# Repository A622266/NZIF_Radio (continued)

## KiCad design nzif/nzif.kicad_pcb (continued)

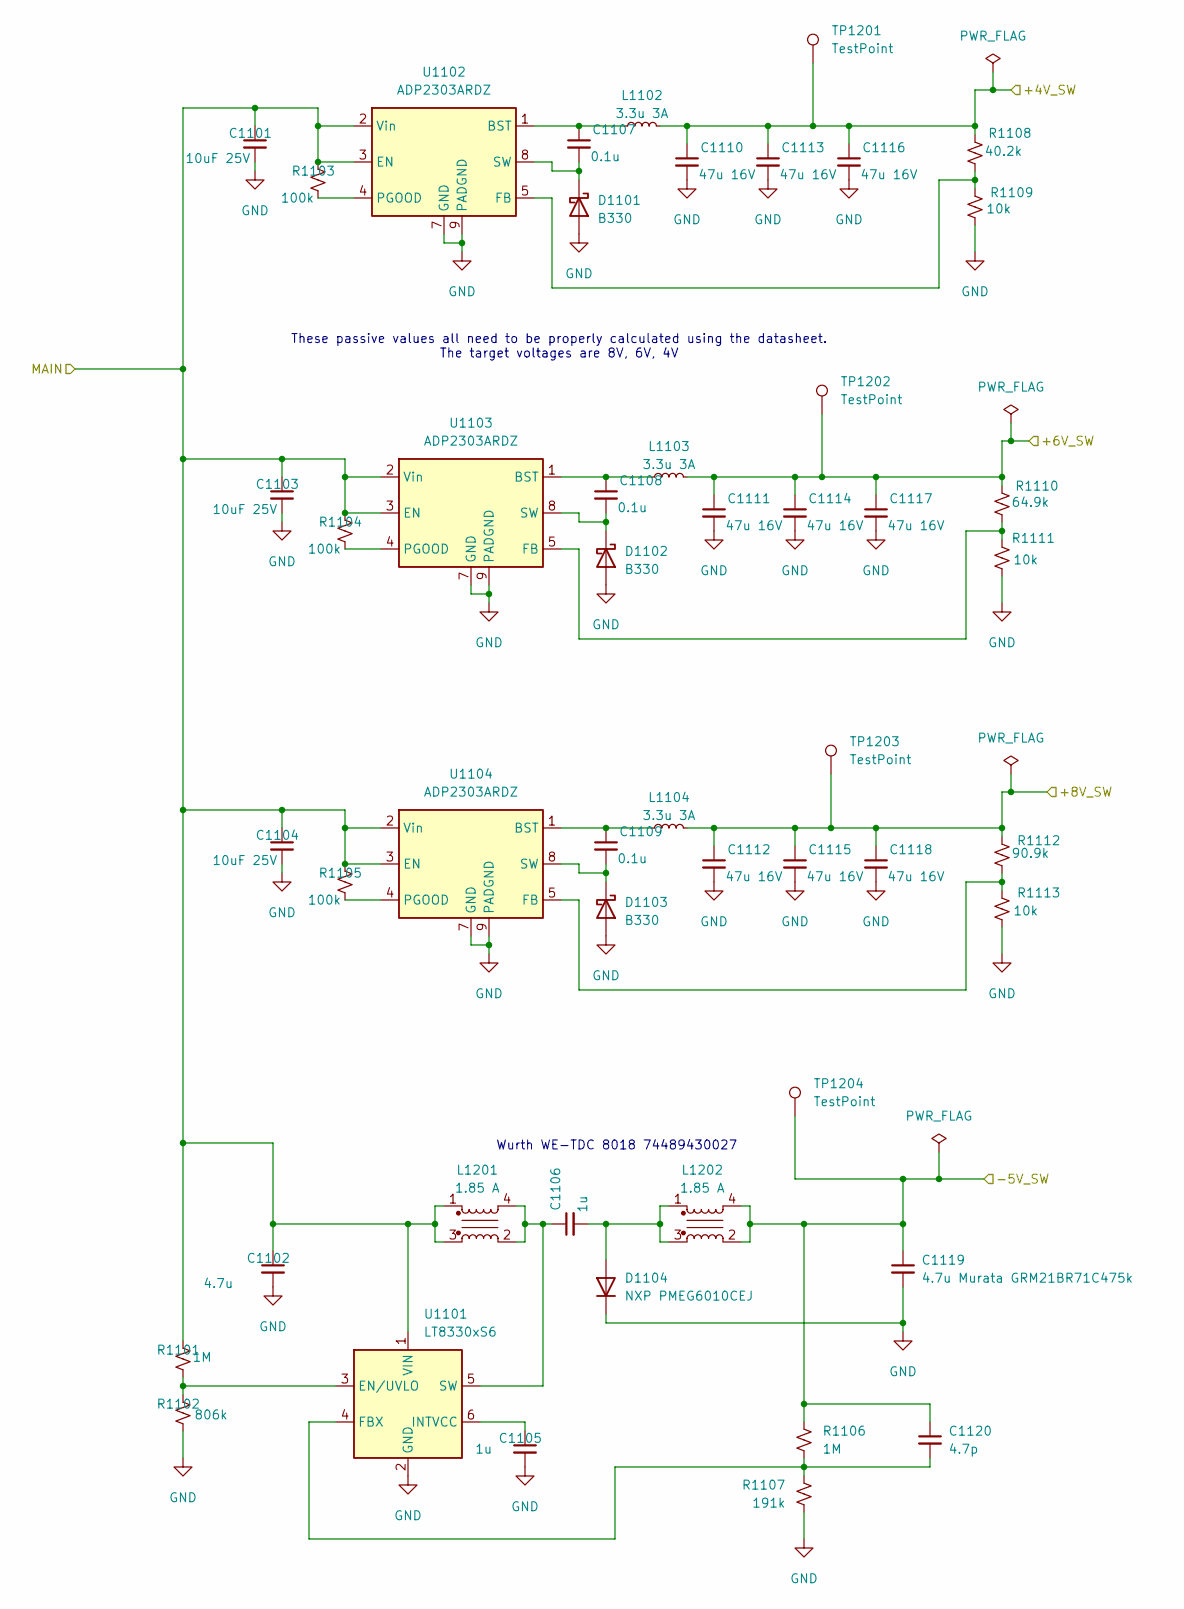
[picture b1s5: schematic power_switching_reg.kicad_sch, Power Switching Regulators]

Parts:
C1101, C1103, C1104: 10uF 25V; C_0402_1005Metric_Pad0.74x0.62mm_HandSolder
C1102: 4.7u; C_0402_1005Metric_Pad0.74x0.62mm_HandSolder
C1105, C1106: 1u; C_0402_1005Metric_Pad0.74x0.62mm_HandSolder
C1107, C1108, C1109: 0.1u; C_0402_1005Metric_Pad0.74x0.62mm_HandSolder
C1110, C1111, C1112, C1113, C1114, C1115, C1116, C1117, C1118: 47u 16V; C_0402_1005Metric_Pad0.74x0.62mm_HandSolder
C1119: 4.7u Murata GRM21BR71C475k; C_0402_1005Metric_Pad0.74x0.62mm_HandSolder
C1120: 4.7p; C_0402_1005Metric_Pad0.74x0.62mm_HandSolder
D1101, D1102, D1103: B330; D_SMC
D1104: NXP PMEG6010CEJ; SMA_Amphenol_901-143_Horizontal
L1102, L1103, L1104: 3.3u 3A; L_Abracon_ASPI-0630LR
L1201, L1202: 8018_74489430027; L_Wurth_WE-TDC-8018; Part Number 74489430027
R1101, R1106: 1M; R_0402_1005Metric_Pad0.72x0.64mm_HandSolder
R1102: 806k; R_0402_1005Metric_Pad0.72x0.64mm_HandSolder
R1103, R1104, R1105: 100k; R_0402_1005Metric_Pad0.72x0.64mm_HandSolder
R1107: 191k; R_0402_1005Metric_Pad0.72x0.64mm_HandSolder
R1108: 40.2k; R_0402_1005Metric_Pad0.72x0.64mm_HandSolder
R1109, R1111, R1113: 10k; R_0402_1005Metric_Pad0.72x0.64mm_HandSolder
R1110: 64.9k; R_0402_1005Metric_Pad0.72x0.64mm_HandSolder
R1112: 90.9k; R_0402_1005Metric_Pad0.72x0.64mm_HandSolder
TP1201, TP1202, TP1203, TP1204: TestPoint; PinHeader_1x01_P1.27mm_Vertical
U1101: LT8330xS6; TSOT-23-6
U1102, U1103, U1104: ADP2303ARDZ; SOIC-8-1EP_3.9x4.9mm_P1.27mm_EP2.29x3mm

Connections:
/6_-_16V: C1101.1, C1102.1, C1103.1, C1104.1, L1201.1, L1201.3, R1101.1, R1103.1, R1104.1, R1105.1, U1101.1 (VIN), U1102.2 (Vin), U1102.3 (EN), U1103.2 (Vin), U1103.3 (EN), U1104.2 (Vin), U1104.3 (EN); also elsewhere on the board
/+4V: C1110.1, C1113.1, C1116.1, L1102.2, R1108.1, TP1201.1 (1_1); also elsewhere on the board
/+6V: C1111.1, C1114.1, C1117.1, L1103.2, R1110.1, TP1202.1 (1_1); also elsewhere on the board
/+8V: C1112.1, C1115.1, C1118.1, L1104.2, R1112.1, TP1203.1 (1_1); also elsewhere on the board
/-5V: C1119.1, C1120.1, L1202.2, L1202.4, R1106.1, TP1204.1 (1_1); also elsewhere on the board
unnamed: C1107.2, D1101.1 (K), U1102.8 (SW)
unnamed: C1108.2, D1102.1 (K), U1103.8 (SW)
unnamed: C1109.2, D1103.1 (K), U1104.8 (SW)
unnamed: C1106.2, D1104.2 (A), L1202.1, L1202.3
unnamed: R1101.2, R1102.1, U1101.3 (EN/UVLO)
unnamed: C1120.2, R1106.2, R1107.1, U1101.4 (FBX)
unnamed: C1105.1, U1101.6 (INTVCC)
unnamed 418: C1106.1, L1201.2, L1201.4, U1101.5 (SW); also elsewhere on the board
unnamed: C1107.1, L1102.1, U1102.1 (BST)
unnamed: R1108.2, R1109.1, U1102.5 (FB)
unnamed: R1103.2, U1102.4 (PGOOD)
unnamed: C1108.1, L1103.1, U1103.1 (BST)
unnamed: R1110.2, R1111.1, U1103.5 (FB)
unnamed: R1104.2, U1103.4 (PGOOD)
unnamed: C1109.1, L1104.1, U1104.1 (BST)
unnamed: R1112.2, R1113.1, U1104.5 (FB)
unnamed: R1105.2, U1104.4 (PGOOD)

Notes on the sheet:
Wurth WE-TDC 8018 74489430027
These passive values all need to be properly calculated using the datasheet. The target voltages are 8V, 6V, 4V

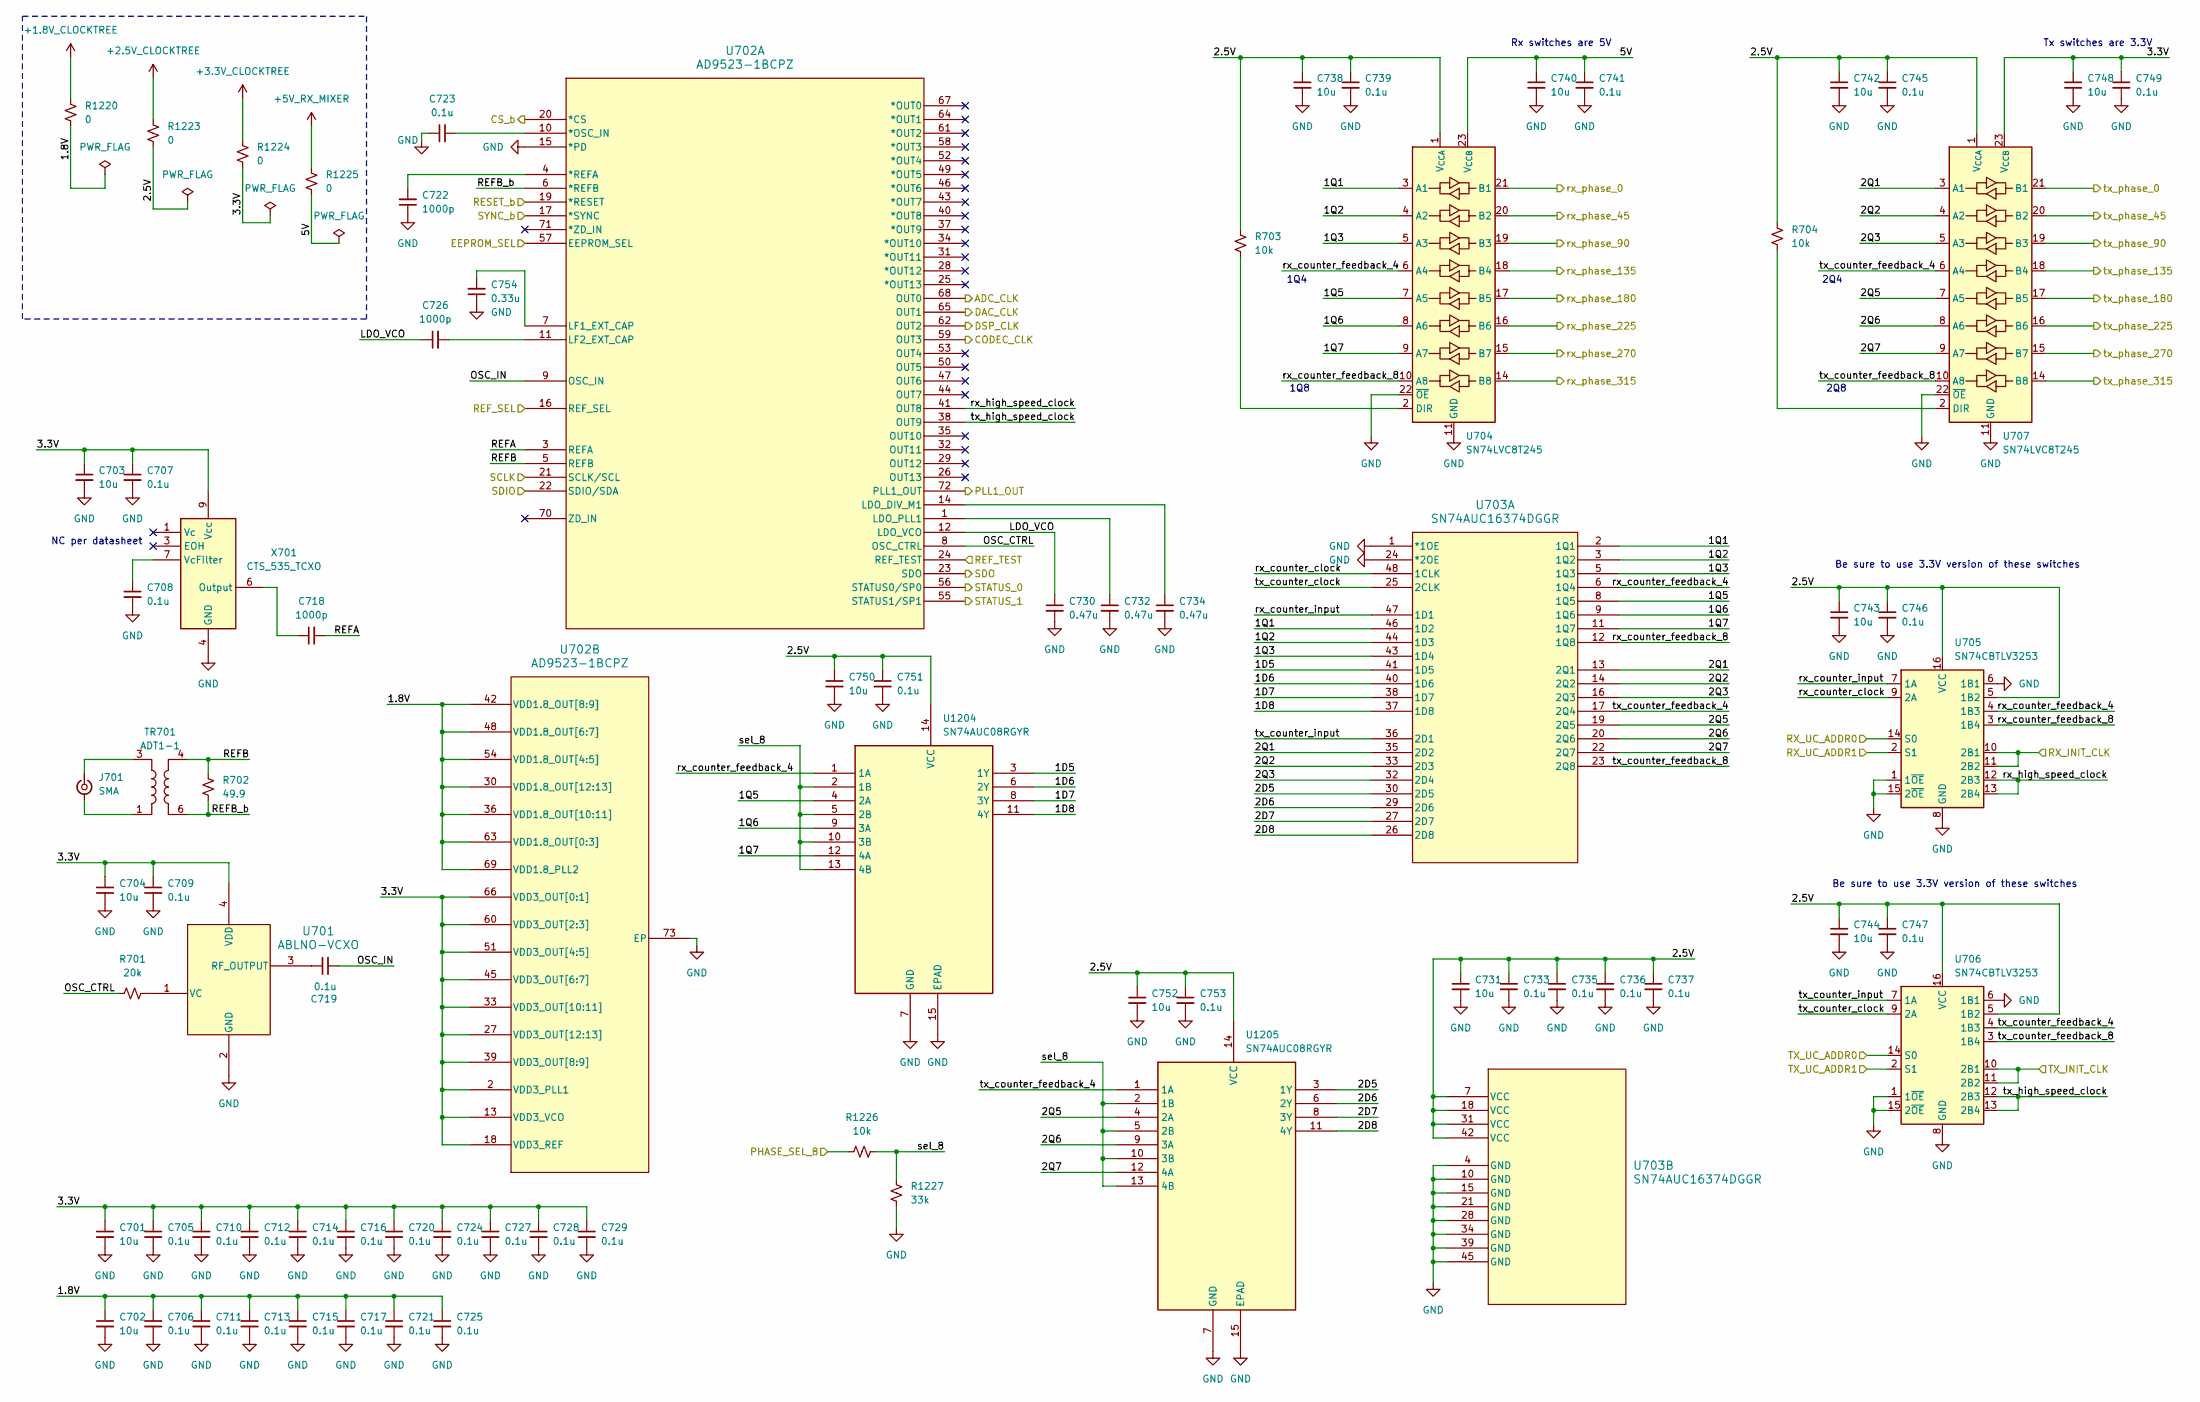
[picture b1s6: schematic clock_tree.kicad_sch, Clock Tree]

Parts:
C701, C702, C703, C704, C731, C738, C740, C742, C743, C744, C748, C750, C752: 10u; C_0402_1005Metric_Pad0.74x0.62mm_HandSolder
C705, C706, C707, C708, C709, C710, C711, C712, C713, C714, C715, C716, C717, C719, C720, C721, C723, C724, C725, C727, C728, C729, C733, C735, C736, C737, C739, C741, C745, C746, C747, C749, C751, C753: 0.1u; C_0402_1005Metric_Pad0.74x0.62mm_HandSolder
C718, C722, C726: 1000p; C_0402_1005Metric_Pad0.74x0.62mm_HandSolder
C730, C732, C734: 0.47u; C_0402_1005Metric_Pad0.74x0.62mm_HandSolder
C754: 0.33u; C_0402_1005Metric_Pad0.74x0.62mm_HandSolder
J701: SMA; SMA_Amphenol_901-143_Horizontal
R701: 20k; R_0402_1005Metric_Pad0.72x0.64mm_HandSolder
R702: 49.9; R_0402_1005Metric_Pad0.72x0.64mm_HandSolder
R703, R704, R1226: 10k; R_0402_1005Metric_Pad0.72x0.64mm_HandSolder
R1220, R1223, R1224, R1225: 0; R_0402_1005Metric_Pad0.72x0.64mm_HandSolder
R1227: 33k; R_0402_1005Metric_Pad0.72x0.64mm_HandSolder
TR701: ADT1-1; Mini-Circuits_CD542_H2.84mm
U701: ABLNO-VCXO; ABLNO_ABR
U702: AD9523-1BCPZ; CP-72-7_ADI
U703: SN74AUC16374DGGR; DGG48
U704, U707: SN74LVC8T245; TSSOP-24_6.1x7.8mm_P0.65mm
U705, U706: SN74CBTLV3253; TSSOP-16_4.4x5mm_P0.65mm
U1204, U1205: SN74AUC08RGYR; RGY14_2P05X2P05
X701: CTS_535_TCXO

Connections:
+1.8V_CLOCKTREE: R1220.1; also elsewhere on the board
+2.5V_CLOCKTREE: R1223.1; also elsewhere on the board
+3.3V_CLOCKTREE: R1224.1; also elsewhere on the board
/ADC_CLK: U702.68 (OUT0); also elsewhere on the board
/CLK_EEPROM_SEL: U702.57 (EEPROM_SEL); also elsewhere on the board
/CLK_REF_SEL: U702.16 (REF_SEL); also elsewhere on the board
/CLK_REF_TEST: U702.24 (REF_TEST); also elsewhere on the board
/CLK_RESET_b: U702.19 (*RESET); also elsewhere on the board
/CLK_SYNC_b: U702.17 (*SYNC); also elsewhere on the board
/CODEC_CLK: U702.59 (OUT3); also elsewhere on the board
/Clock_Tree/1.8V: C702.1, C706.1, C711.1, C713.1, C715.1, C717.1, C721.1, C725.1, R1220.2, U702.30 (VDD1.8_OUT[12:13]), U702.36 (VDD1.8_OUT[10:11]), U702.42 (VDD1.8_OUT[8:9]), U702.48 (VDD1.8_OUT[6:7]), U702.54 (VDD1.8_OUT[4:5]), U702.63 (VDD1.8_OUT[0:3]), U702.69 (VDD1.8_PLL2)
/Clock_Tree/1D5: U703.41 (1D5), U1204.3 (1Y)
/Clock_Tree/1D6: U703.40 (1D6), U1204.6 (2Y)
/Clock_Tree/1D7: U703.38 (1D7), U1204.8 (3Y)
/Clock_Tree/1D8: U703.37 (1D8), U1204.11 (4Y)
/Clock_Tree/1Q1: U703.2 (1Q1), U703.46 (1D2), U704.3 (A1)
/Clock_Tree/1Q2: U703.3 (1Q2), U703.44 (1D3), U704.4 (A2)
/Clock_Tree/1Q3: U703.5 (1Q3), U703.43 (1D4), U704.5 (A3)
/Clock_Tree/1Q5: U703.8 (1Q5), U704.7 (A5), U1204.4 (2A)
/Clock_Tree/1Q6: U703.9 (1Q6), U704.8 (A6), U1204.9 (3A)
/Clock_Tree/1Q7: U703.11 (1Q7), U704.9 (A7), U1204.12 (4A)
/Clock_Tree/2.5V: C731.1, C733.1, C735.1, C736.1, C737.1, C738.1, C739.1, C742.1, C743.1, C744.1, C745.1, C746.1, C747.1, C750.1, C751.1, C752.1, C753.1, R703.1, R704.1, R1223.2, U703.7 (VCC), U703.18 (VCC), U703.31 (VCC), U703.42 (VCC), U704.1 (V_{CCA}), U705.5 (1B2), U705.16 (VCC), U706.5 (1B2), U706.16 (VCC), U707.1 (V_{CCA}), U1204.14 (VCC), U1205.14 (VCC)
/Clock_Tree/2D5: U703.30 (2D5), U1205.3 (1Y)
/Clock_Tree/2D6: U703.29 (2D6), U1205.6 (2Y)
/Clock_Tree/2D7: U703.27 (2D7), U1205.8 (3Y)
/Clock_Tree/2D8: U703.26 (2D8), U1205.11 (4Y)
/Clock_Tree/2Q1: U703.13 (2Q1), U703.35 (2D2), U707.3 (A1)
/Clock_Tree/2Q2: U703.14 (2Q2), U703.33 (2D3), U707.4 (A2)
/Clock_Tree/2Q3: U703.16 (2Q3), U703.32 (2D4), U707.5 (A3)
/Clock_Tree/2Q5: U703.19 (2Q5), U707.7 (A5), U1205.4 (2A)
/Clock_Tree/2Q6: U703.20 (2Q6), U707.8 (A6), U1205.9 (3A)
/Clock_Tree/2Q7: U703.22 (2Q7), U707.9 (A7), U1205.12 (4A)
/Clock_Tree/3.3V: C701.1, C703.1, C704.1, C705.1, C707.1, C709.1, C710.1, C712.1, C714.1, C716.1, C720.1, C724.1, C727.1, C728.1, C729.1, C748.1, C749.1, R1224.2, U701.4 (VDD), U702.2 (VDD3_PLL1), U702.13 (VDD3_VCO), U702.18 (VDD3_REF), U702.27 (VDD3_OUT[12:13]), U702.33 (VDD3_OUT[10:11]), U702.39 (VDD3_OUT[8:9]), U702.45 (VDD3_OUT[6:7]), U702.51 (VDD3_OUT[4:5]), U702.60 (VDD3_OUT[2:3]), U702.66 (VDD3_OUT[0:1]), U707.23 (V_{CCB}), U707.24 (V_{CCB}), X701.9 (Vcc)
/Clock_Tree/5V: C740.1, C741.1, R1225.2, U704.23 (V_{CCB}), U704.24 (V_{CCB})
/Clock_Tree/LDO_VCO: C726.1, C730.1, U702.12 (LDO_VCO)
/Clock_Tree/OSC_CTRL: R701.1, U702.8 (OSC_CTRL)
/Clock_Tree/OSC_IN: C719.2, U702.9 (OSC_IN)
/Clock_Tree/PLL1_OUT: U702.72 (PLL1_OUT); also elsewhere on the board
/Clock_Tree/REFA: C718.2, U702.3 (REFA)
/Clock_Tree/REFB: R702.1, TR701.4, U702.5 (REFB)
/Clock_Tree/REFB_b: R702.2, TR701.6, U702.6 (*REFB)
/Clock_Tree/STATUS_0: U702.56 (STATUS0/SP0); also elsewhere on the board
/Clock_Tree/STATUS_1: U702.55 (STATUS1/SP1); also elsewhere on the board
/Clock_Tree/rx_counter_clock: U703.48 (1CLK), U705.9 (2A)
/Clock_Tree/rx_counter_feedback_4: U703.6 (1Q4), U704.6 (A4), U705.4 (1B3), U1204.1 (1A)
/Clock_Tree/rx_counter_feedback_8: U703.12 (1Q8), U704.10 (A8), U705.3 (1B4)
/Clock_Tree/rx_counter_input: U703.47 (1D1), U705.7 (1A)
/Clock_Tree/rx_high_speed_clock: U702.41 (OUT8), U705.12 (2B3), U705.13 (2B4)
/Clock_Tree/rx_phase_0: U704.21 (B1); also elsewhere on the board
/Clock_Tree/rx_phase_45: U704.20 (B2); also elsewhere on the board
/Clock_Tree/rx_phase_90: U704.19 (B3); also elsewhere on the board
/Clock_Tree/rx_phase_135: U704.18 (B4); also elsewhere on the board
/Clock_Tree/rx_phase_180: U704.17 (B5); also elsewhere on the board
/Clock_Tree/rx_phase_225: U704.16 (B6); also elsewhere on the board
/Clock_Tree/rx_phase_270: U704.15 (B7); also elsewhere on the board
/Clock_Tree/rx_phase_315: U704.14 (B8); also elsewhere on the board
/Clock_Tree/sel_8: R1226.2, R1227.1, U1204.2 (1B), U1204.5 (2B), U1204.10 (3B), U1204.13 (4B), U1205.2 (1B), U1205.5 (2B), U1205.10 (3B), U1205.13 (4B)
/Clock_Tree/tx_counter_clock: U703.25 (2CLK), U706.9 (2A)
/Clock_Tree/tx_counter_feedback_4: U703.17 (2Q4), U706.4 (1B3), U707.6 (A4), U1205.1 (1A)
/Clock_Tree/tx_counter_feedback_8: U703.23 (2Q8), U706.3 (1B4), U707.10 (A8)
/Clock_Tree/tx_counter_input: U703.36 (2D1), U706.7 (1A)
/Clock_Tree/tx_high_speed_clock: U702.38 (OUT9), U706.12 (2B3), U706.13 (2B4)
/Clock_Tree/tx_phase_0: U707.21 (B1); also elsewhere on the board
/Clock_Tree/tx_phase_45: U707.20 (B2); also elsewhere on the board
/Clock_Tree/tx_phase_90: U707.19 (B3); also elsewhere on the board
/Clock_Tree/tx_phase_135: U707.18 (B4); also elsewhere on the board
/Clock_Tree/tx_phase_180: U707.17 (B5); also elsewhere on the board
/Clock_Tree/tx_phase_225: U707.16 (B6); also elsewhere on the board
/Clock_Tree/tx_phase_270: U707.15 (B7); also elsewhere on the board
/Clock_Tree/tx_phase_315: U707.14 (B8); also elsewhere on the board
/DAC_CLK: U702.65 (OUT1); also elsewhere on the board
/DSP_CLK: U702.62 (OUT2); also elsewhere on the board
/PHASE_SEL_8: R1226.1; also elsewhere on the board
/RX_CLK_ADDR0: U705.14 (S0); also elsewhere on the board
/RX_CLK_ADDR1: U705.2 (S1); also elsewhere on the board
/RX_INIT_CLK: U705.10 (2B1), U705.11 (2B2); also elsewhere on the board
/SPI0_RX: U702.23 (SDO); also elsewhere on the board
/SPI0_SC0: U702.20 (*CS); also elsewhere on the board
/SPI0_TX: U702.22 (SDIO/SDA); also elsewhere on the board
/SPIO_SCLK: U702.21 (SCLK/SCL); also elsewhere on the board
/TX_CLK_ADDR0: U706.14 (S0); also elsewhere on the board
/TX_CLK_ADDR1: U706.2 (S1); also elsewhere on the board
/TX_INIT_CLK: U706.10 (2B1), U706.11 (2B2); also elsewhere on the board
unnamed: J701.2 (Ext), TR701.1
unnamed: J701.1 (In), TR701.3
unnamed: C719.1, U701.3 (RF_OUTPUT)
unnamed: R701.2, U701.1 (VC)
unnamed: C723.2, U702.10 (*OSC_IN)
unnamed: C722.2, U702.4 (*REFA)
unnamed: C734.1, U702.14 (LDO_DIV_M1)
unnamed: C732.1, U702.1 (LDO_PLL1)
unnamed: C754.2, U702.7 (LF1_EXT_CAP)
unnamed: C726.2, U702.11 (LF2_EXT_CAP)
unnamed: R703.2, U704.2 (DIR)
unnamed: R704.2, U707.2 (DIR)
unnamed: C718.1, X701.6 (Output)
unnamed: C708.1, X701.7 (VcFilter)

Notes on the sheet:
Rx switches are 5V
Be sure to use 3.3V version of these switches
1Q4
Tx switches are 3.3V
1Q8
2Q4
NC per datasheet
2Q8

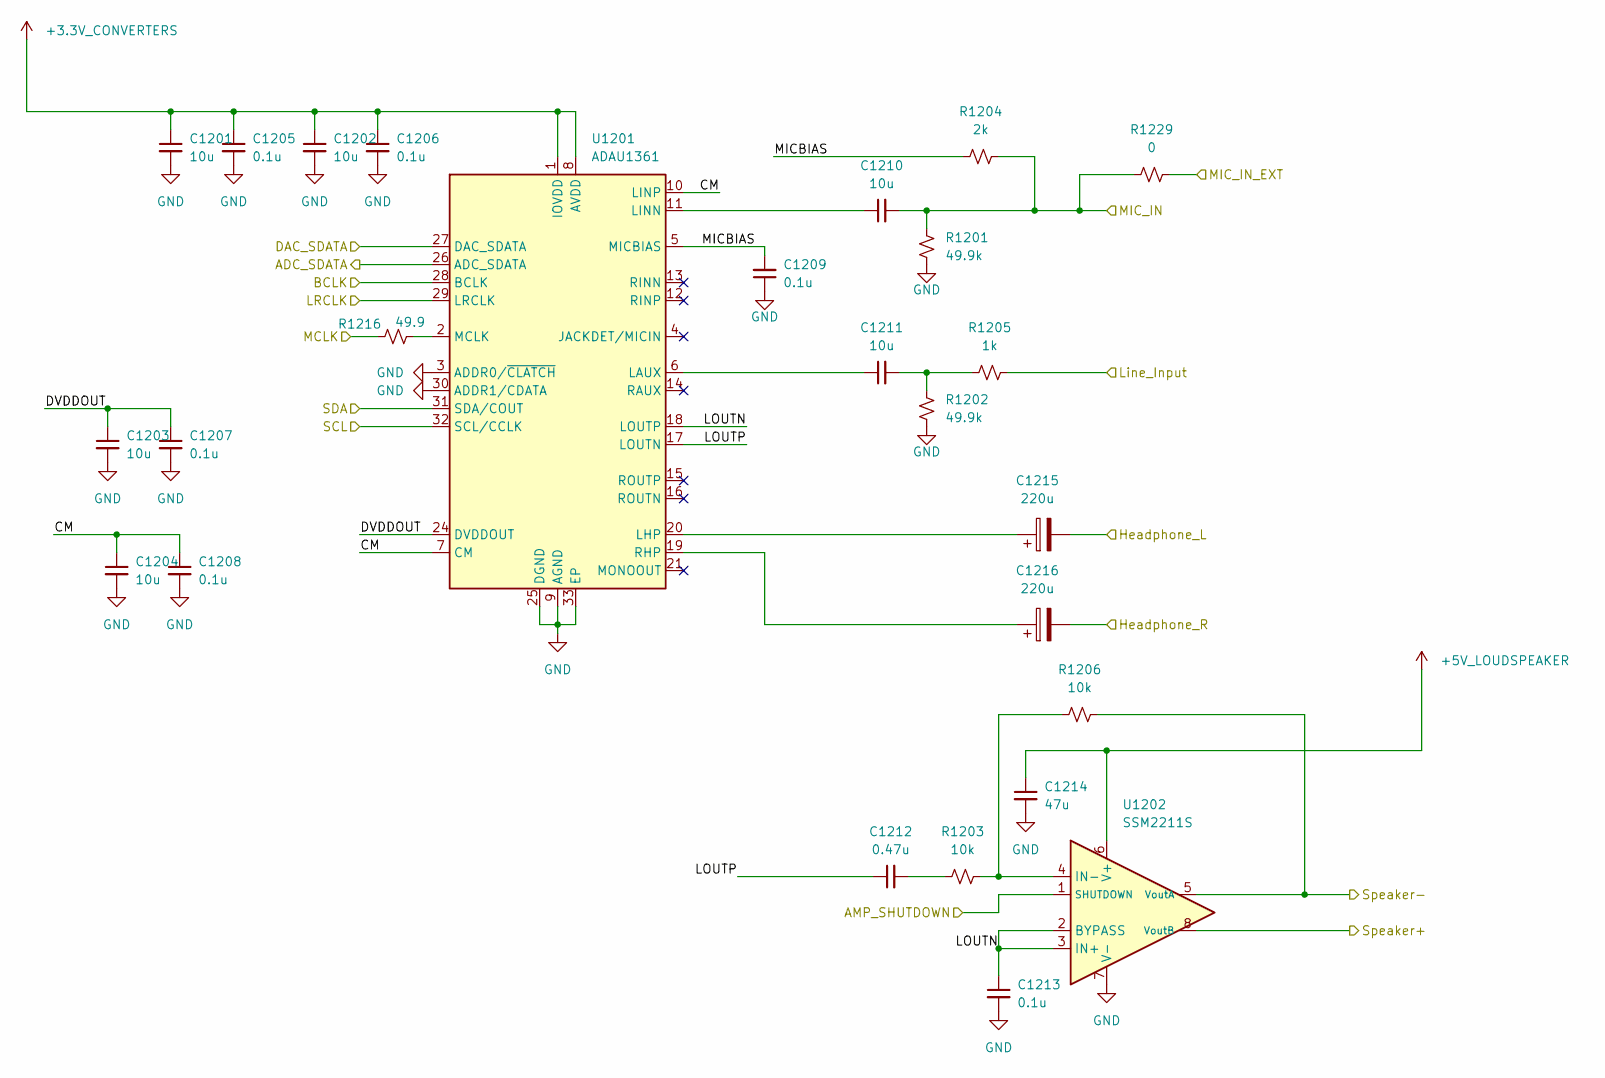
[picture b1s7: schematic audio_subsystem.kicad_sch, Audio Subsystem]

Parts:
C1201, C1202, C1203, C1204, C1210, C1211: 10u; C_0402_1005Metric_Pad0.74x0.62mm_HandSolder
C1205, C1206, C1207, C1208, C1209, C1213: 0.1u; C_0402_1005Metric_Pad0.74x0.62mm_HandSolder
C1212: 0.47u; C_0402_1005Metric_Pad0.74x0.62mm_HandSolder
C1214: 47u; C_0402_1005Metric_Pad0.74x0.62mm_HandSolder
C1215, C1216: 220u; CP_Elec_6.3x7.7; Digikey Part # UWT1C221MCL1GS
R1201, R1202: 49.9k; R_0402_1005Metric_Pad0.72x0.64mm_HandSolder
R1203, R1206: 10k; R_0402_1005Metric_Pad0.72x0.64mm_HandSolder
R1204: 2k; R_0402_1005Metric_Pad0.72x0.64mm_HandSolder
R1205: 1k; R_0402_1005Metric_Pad0.72x0.64mm_HandSolder
R1216: 49.9; R_0402_1005Metric_Pad0.72x0.64mm_HandSolder
R1229: 0; R_0402_1005Metric_Pad0.72x0.64mm_HandSolder
U1201: ADAU1361; LFCSP-32-1EP_5x5mm_P0.5mm_EP3.5x3.5mm_ThermalVias
U1202: SSM2211S; SOIC-8_3.9x4.9mm_P1.27mm

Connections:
+3.3V_CONVERTERS: C1201.1, C1202.1, C1205.1, C1206.1, U1201.1 (IOVDD), U1201.8 (AVDD), U1201.23 (AVDD); also elsewhere on the board
+5V_LOUDSPEAKER: C1214.1, U1202.6 (V+); also elsewhere on the board
/AMP_SHUTDOWN: U1202.1 (SHUTDOWN); also elsewhere on the board
/Audio_Subsystem/ADC_SDATA: U1201.26 (ADC_SDATA); also elsewhere on the board
/Audio_Subsystem/BCLK: U1201.28 (BCLK); also elsewhere on the board
/Audio_Subsystem/CM: C1204.1, C1208.1, U1201.7 (CM), U1201.10 (LINP)
/Audio_Subsystem/DAC_SDATA: U1201.27 (DAC_SDATA); also elsewhere on the board
/Audio_Subsystem/DVDDOUT: C1203.1, C1207.1, U1201.24 (DVDDOUT)
/Audio_Subsystem/Headphone_L: C1215.2; also elsewhere on the board
/Audio_Subsystem/Headphone_R: C1216.2; also elsewhere on the board
/Audio_Subsystem/LOUTN: C1213.1, U1201.18 (LOUTP), U1202.2 (BYPASS), U1202.3 (IN+)
/Audio_Subsystem/LOUTP: C1212.1, U1201.17 (LOUTN)
/Audio_Subsystem/LRCLK: U1201.29 (LRCLK); also elsewhere on the board
/Audio_Subsystem/Line_Input: R1205.2; also elsewhere on the board
/Audio_Subsystem/MICBIAS: C1209.2, R1204.1, U1201.5 (MICBIAS)
/Audio_Subsystem/MIC_IN: C1210.2, R1201.1, R1204.2, R1229.1; also elsewhere on the board
/Audio_Subsystem/MIC_IN_EXT: R1229.2; also elsewhere on the board
/Audio_Subsystem/Speaker+: U1202.8 (VoutB); also elsewhere on the board
/Audio_Subsystem/Speaker-: R1206.2, U1202.5 (VoutA); also elsewhere on the board
/CODEC_CLK: R1216.1; also elsewhere on the board
/SCL0: U1201.32 (SCL/CCLK); also elsewhere on the board
/SDA0: U1201.31 (SDA/COUT); also elsewhere on the board
unnamed: C1211.2, R1202.1, R1205.1
unnamed: C1212.2, R1203.1
unnamed: C1211.1, U1201.6 (LAUX)
unnamed: C1215.1, U1201.20 (LHP)
unnamed: C1210.1, U1201.11 (LINN)
unnamed: R1216.2, U1201.2 (MCLK)
unnamed: C1216.1, U1201.19 (RHP)
unnamed: R1203.2, R1206.1, U1202.4 (IN-)

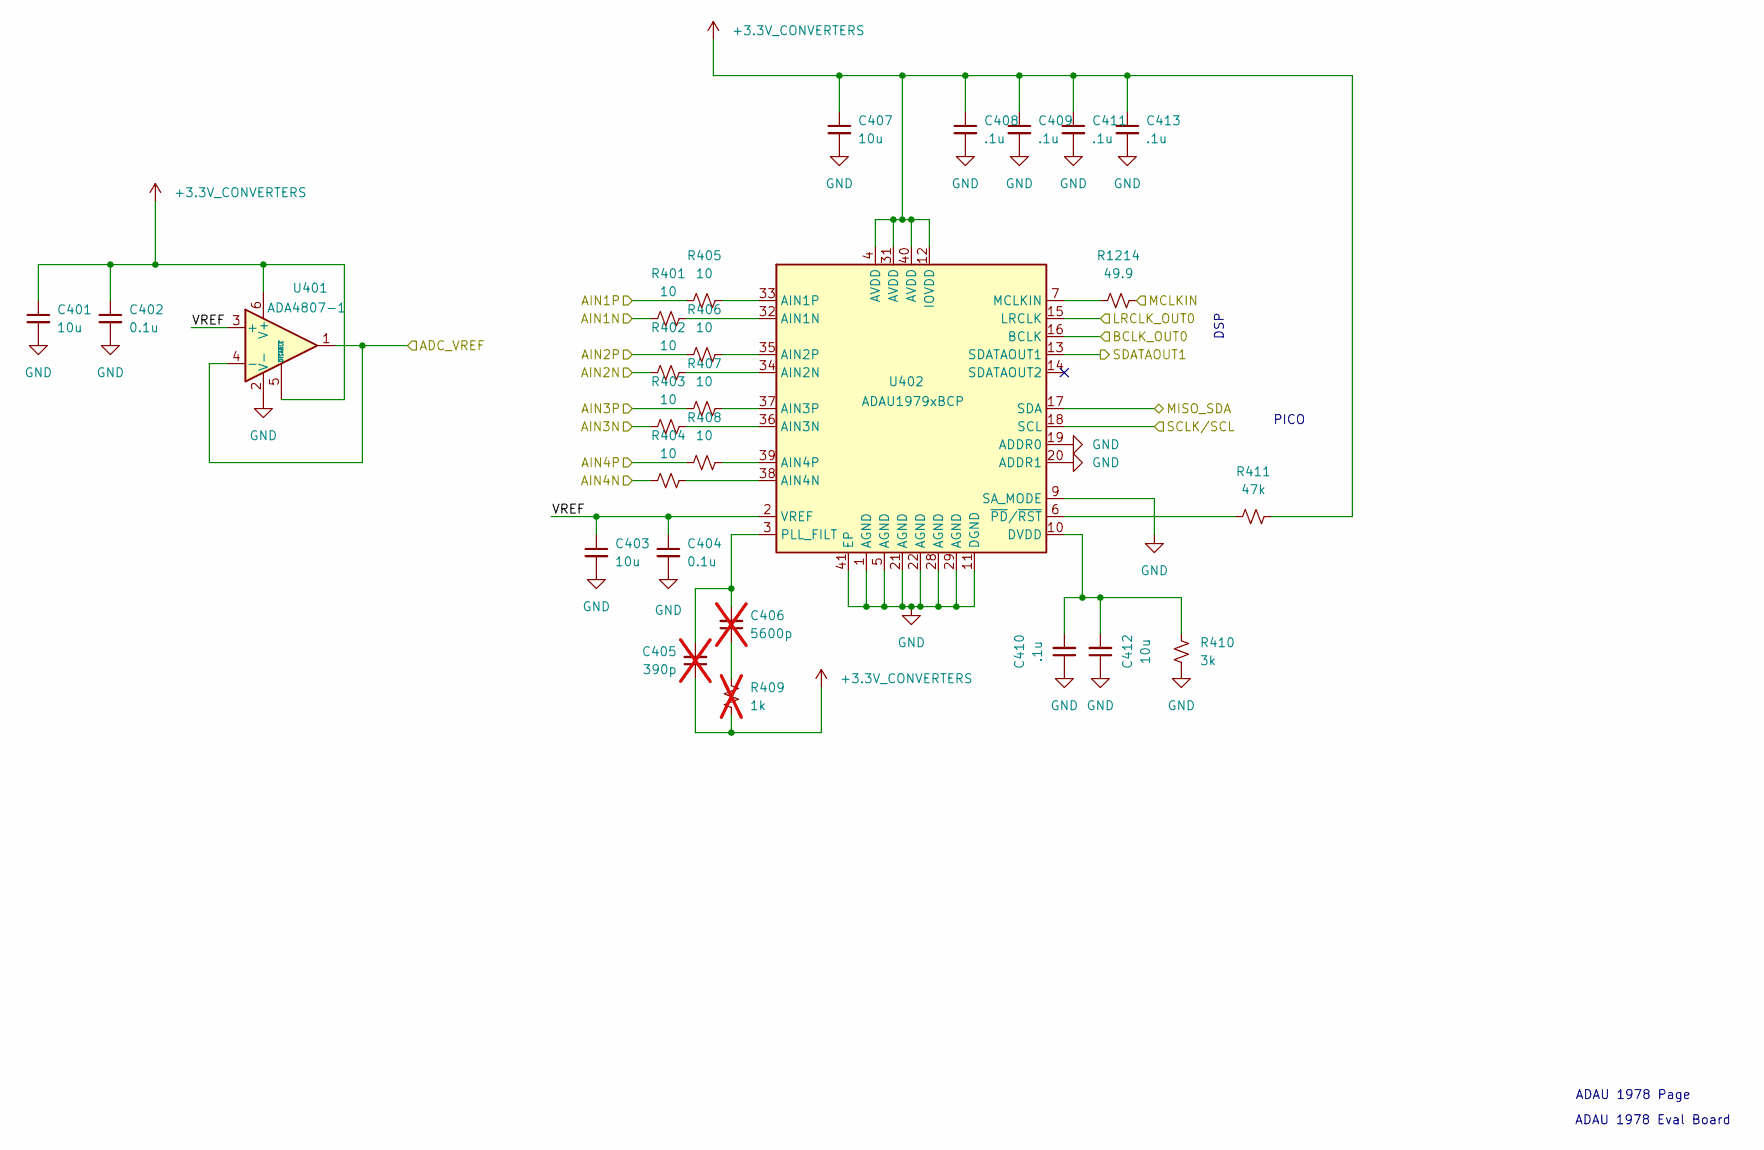
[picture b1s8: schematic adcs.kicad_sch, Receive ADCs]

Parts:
C401, C403: 10u; C_0402_1005Metric_Pad0.74x0.62mm_HandSolder; Digikey Part # 587-3258-1-ND
C402, C404: 0.1u; C_0402_1005Metric_Pad0.74x0.62mm_HandSolder; Digikey Part # 490-GCM31C5C1H104FA16LCT-ND
C405: 390p; C_0402_1005Metric_Pad0.74x0.62mm_HandSolder; not fitted
C406: 5600p; C_0402_1005Metric_Pad0.74x0.62mm_HandSolder; not fitted
C407, C412: 10u; C_0402_1005Metric_Pad0.74x0.62mm_HandSolder
C408, C409, C410, C411, C413: .1u; C_0402_1005Metric_Pad0.74x0.62mm_HandSolder
R401, R402, R403, R404, R405, R406, R407, R408: 10; R_0402_1005Metric_Pad0.72x0.64mm_HandSolder
R409: 1k; R_0402_1005Metric_Pad0.72x0.64mm_HandSolder; not fitted
R410: 3k; R_0402_1005Metric_Pad0.72x0.64mm_HandSolder
R411: 47k; R_0402_1005Metric_Pad0.72x0.64mm_HandSolder
R1214: 49.9; R_0402_1005Metric_Pad0.72x0.64mm_HandSolder
U401: ADA4807-1; SOT-23-6
U402: ADAU1979xBCP; LFCSP-40-1EP_6x6mm_P0.5mm_EP3.9x3.9mm

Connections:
+3.3V_CONVERTERS: C401.1, C402.1, C405.1, C407.1, C408.1, C409.1, C411.1, C413.1, R409.1, R411.2, U401.5 (~DISABLE), U401.6 (V+), U402.4 (AVDD), U402.12 (IOVDD), U402.31 (AVDD), U402.40 (AVDD); also elsewhere on the board
/ADC_CLK: R1214.2; also elsewhere on the board
/ADCs/ADC_VREF: U401.1, U401.4 (-); also elsewhere on the board
/ADCs/AIN1N: R401.1; also elsewhere on the board
/ADCs/AIN1P: R405.1; also elsewhere on the board
/ADCs/AIN2N: R402.1; also elsewhere on the board
/ADCs/AIN2P: R406.1; also elsewhere on the board
/ADCs/AIN3N: R403.1; also elsewhere on the board
/ADCs/AIN3P: R407.1; also elsewhere on the board
/ADCs/AIN4N: R404.1; also elsewhere on the board
/ADCs/AIN4P: R408.1; also elsewhere on the board
/ADCs/BCLK_OUT0: U402.16 (BCLK); also elsewhere on the board
/ADCs/LRCLK_OUT0: U402.15 (LRCLK); also elsewhere on the board
/ADCs/SDATAOUT1: U402.13 (SDATAOUT1); also elsewhere on the board
/ADCs/VREF: C403.1, C404.1, U401.3 (+), U402.2 (VREF)
/SCL0: U402.18 (SCL); also elsewhere on the board
/SDA0: U402.17 (SDA); also elsewhere on the board
unnamed: C406.1, R409.2
unnamed: R401.2, U402.32 (AIN1N)
unnamed: R405.2, U402.33 (AIN1P)
unnamed: R402.2, U402.34 (AIN2N)
unnamed: R406.2, U402.35 (AIN2P)
unnamed: R403.2, U402.36 (AIN3N)
unnamed: R407.2, U402.37 (AIN3P)
unnamed: R404.2, U402.38 (AIN4N)
unnamed: R408.2, U402.39 (AIN4P)
unnamed: C410.2, C412.2, R410.2, U402.10 (DVDD)
unnamed: R1214.1, U402.7 (MCLKIN)
unnamed: C405.2, C406.2, U402.3 (PLL_FILT)
unnamed: R411.1, U402.6 (~PD/~RST)

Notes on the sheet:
ADAU 1978 Page
ADAU 1978 Eval Board
PICO
DSP

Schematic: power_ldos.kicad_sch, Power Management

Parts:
C901, C902, C903, C911, C912, C919, C920, C921: 4.7u; C_0402_1005Metric_Pad0.74x0.62mm_HandSolder
C904, C905, C906, C910, C913, C914, C915, C922, C923, C924, C929: 0.47u; C_0402_1005Metric_Pad0.74x0.62mm_HandSolder
C907, C908, C909, C916, C917, C918, C925, C926, C927, C930, C931: 10u; C_0402_1005Metric_Pad0.74x0.62mm_HandSolder
C928: 10u; C_0402_1005Metric_Pad0.74x0.62mm_HandSolder; Digikey Part # 587-3258-1-ND
R901, R903, R905, R906, R907, R908: 49.9k; R_0402_1005Metric_Pad0.72x0.64mm_HandSolder
R902: 33.2k; R_0402_1005Metric_Pad0.72x0.64mm_HandSolder
R904: 34.8k; R_0402_1005Metric_Pad0.72x0.64mm_HandSolder
R909: 18k; R_0402_1005Metric_Pad0.72x0.64mm_HandSolder
R910: 16.5k; R_0402_1005Metric_Pad0.72x0.64mm_HandSolder
R911, R912: 20m; R_0402_1005Metric_Pad0.72x0.64mm_HandSolder
TP1205, TP1206, TP1207, TP1208, TP1209, TP1210, TP1211, TP1212, TP1213, TP1214: TestPoint; PinHeader_1x01_P1.27mm_Vertical
U901, U902, U903, U905, U906, U907, U908, U909, U910, U911: LT3045xMSE; MSOP-12-1EP_3x4.039mm_P0.65mm_EP1.651x2.845mm
U904: LT3094EDD-PBF; DD_05-08-1725_ADI

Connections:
+1.8V_CLOCKTREE: C927.1, TP1212.1 (1_1), U909.10 (OUTS), U909.11 (OUT), U909.12 (OUT); also elsewhere on the board
+2.5V_CLOCKTREE: C925.1, TP1213.1 (1_1), U907.10 (OUTS), U907.11 (OUT), U907.12 (OUT); also elsewhere on the board
+3.3V_CLOCKTREE: C926.1, TP1208.1 (1_1), U908.10 (OUTS), U908.11 (OUT), U908.12 (OUT); also elsewhere on the board
+3.3V_CONVERTERS: C907.1, TP1206.1 (1_1), U901.10 (OUTS), U901.11 (OUT), U901.12 (OUT); also elsewhere on the board
+3.3V_DSP_UC: R911.2, R912.2, TP1214.1 (1_1); also elsewhere on the board
+3.3V_TX_MIXER: C916.1, TP1209.1 (1_1), U905.10 (OUTS), U905.11 (OUT), U905.12 (OUT); also elsewhere on the board
+5V_LOUDSPEAKER: C917.1, TP1210.1 (1_1), U906.10 (OUTS), U906.11 (OUT), U906.12 (OUT); also elsewhere on the board
+6.5V_RX_OPAMPS: C909.1, TP1207.1 (1_1), U903.10 (OUTS), U903.11 (OUT), U903.12 (OUT); also elsewhere on the board
-3.5V_RX_OPAMPS: C918.1, TP1211.1 (1_1), U904.10 (OUTS), U904.11 (OUT), U904.12 (OUT); also elsewhere on the board
/+4V: C901.1, C919.1, C920.1, C921.1, C928.1, U901.1 (IN), U901.2 (IN), U901.3 (IN), U901.4 (EN/UV), U901.7 (PGFB), U907.1 (IN), U907.2 (IN), U907.3 (IN), U907.4 (EN/UV), U907.7 (PGFB), U908.1 (IN), U908.2 (IN), U908.3 (IN), U908.4 (EN/UV), U908.7 (PGFB), U909.1 (IN), U909.2 (IN), U909.3 (IN), U909.4 (EN/UV), U909.7 (PGFB), U910.1 (IN), U910.2 (IN), U910.3 (IN), U910.4 (EN/UV), U910.7 (PGFB), U911.1 (IN), U911.2 (IN), U911.3 (IN), U911.4 (EN/UV), U911.7 (PGFB); also elsewhere on the board
/+6V: C902.1, C911.1, C912.1, U902.1 (IN), U902.2 (IN), U902.3 (IN), U902.4 (EN/UV), U902.7 (PGFB), U905.1 (IN), U905.2 (IN), U905.3 (IN), U905.4 (EN/UV), U905.7 (PGFB), U906.1 (IN), U906.2 (IN), U906.3 (IN), U906.4 (EN/UV), U906.7 (PGFB); also elsewhere on the board
/+8V: C903.1, U903.1 (IN), U903.2 (IN), U903.3 (IN), U903.4 (EN/UV), U903.7 (PGFB); also elsewhere on the board
/-5V: C913.1, U904.1 (IN), U904.2 (IN), U904.3 (EN/UV), U904.5 (PGFB), U904.13 (IN); also elsewhere on the board
unnamed: C905.1, R902.1, U901.8 (SET)
unnamed: C904.1, R901.1, U902.8 (SET)
unnamed: C906.1, R903.1, U903.8 (SET)
unnamed: C910.1, R904.1, U904.8 (SET)
unnamed: C914.1, R905.1, U905.8 (SET)
unnamed: C915.1, R906.1, U906.8 (SET)
unnamed: C922.1, R907.1, U907.8 (SET)
unnamed: C923.1, R908.1, U908.8 (SET)
unnamed: C924.1, R909.1, U909.8 (SET)
unnamed: C930.1, R911.1, U910.10 (OUTS), U910.11 (OUT), U910.12 (OUT)
unnamed: C929.1, R910.1, U910.8 (SET), U911.8 (SET)
unnamed: C931.1, R912.1, U911.10 (OUTS), U911.11 (OUT), U911.12 (OUT)

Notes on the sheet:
3.3V Power for ADCs/DACs/Codec
3.3V Power for DSP and uC
Resistor sets 3.3V output Use high quality cap such as COG
3.3V Power for Tx Switches
2.5V Power for Clock Tree
6.5V Power for RX op amps
Resistor sets 2.5V output Use high quality cap such as COG
Resistor sets 1.8V output Use high quality cap such as COG
checked rset resistor
Resistor sets 5V output Use high quality cap such as COG
Resistor sets 6.5V output Use high quality cap such as COG
1.8V Power for Clock Tree
5V Power for Loudspeaker
3.3V Power for VFO
5V Power for RX Mixer Switches
-3.5V Power for RX op amps

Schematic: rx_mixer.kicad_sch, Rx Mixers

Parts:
C201, C202, C205, C206: 10u; C_0402_1005Metric_Pad0.74x0.62mm_HandSolder; Digikey Part # 587-3258-1-ND
C203, C204, C207, C208: 0.1u; C_0402_1005Metric_Pad0.74x0.62mm_HandSolder; Digikey Part # 490-GCM31C5C1H104FA16LCT-ND
HC_201, HC_202, HC_203, HC_204, HC_205, HC_206, HC_207, HC_208: 2n; C_1206_3216Metric_Pad1.33x1.80mm_HandSolder; Digikey Part # 490-GCM31C5C1H104FA16LCT-ND
U201, U202, U205, U208: ADA4625-2; SOIC-8-1EP_3.9x4.9mm_P1.27mm_EP2.29x3mm; Digikey Part # 505-ADA4625-2ARDZ-R7CT-ND
U203, U204, U206, U207: SN74CBT3125C; TSSOP-14-1EP_4.4x5mm_P0.65mm; Digikey Part # 296-SN74CBT3125CPWRTR-ND

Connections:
+6.5V_RX_OPAMPS: U201.8 (V+), U202.8 (V+), U205.8 (V+), U208.8 (V+); also elsewhere on the board
-3.5V_RX_OPAMPS: U201.4 (V-), U201.9 (EP), U202.4 (V-), U202.9 (EP), U205.4 (V-), U205.9 (EP), U208.4 (V-), U208.9 (EP); also elsewhere on the board
/Clock_Tree/rx_phase_0: U203.1 (*1OE), U206.4 (*2OE); also elsewhere on the board
/Clock_Tree/rx_phase_45: U204.1 (*1OE), U206.13 (*4OE); also elsewhere on the board
/Clock_Tree/rx_phase_90: U203.10 (*3OE), U207.4 (*2OE); also elsewhere on the board
/Clock_Tree/rx_phase_135: U204.10 (*3OE), U207.13 (*4OE); also elsewhere on the board
/Clock_Tree/rx_phase_180: U203.4 (*2OE), U206.1 (*1OE); also elsewhere on the board
/Clock_Tree/rx_phase_225: U204.4 (*2OE), U206.10 (*3OE); also elsewhere on the board
/Clock_Tree/rx_phase_270: U203.13 (*4OE), U207.1 (*1OE); also elsewhere on the board
/Clock_Tree/rx_phase_315: U204.13 (*4OE), U207.10 (*3OE); also elsewhere on the board
/RX_Driver_Amps/P0_IN+: U201.1, U201.2 (-); also elsewhere on the board
/RX_Driver_Amps/P0_IN-: U201.6 (-), U201.7; also elsewhere on the board
/RX_Driver_Amps/P45_IN+: U205.1, U205.2 (-); also elsewhere on the board
/RX_Driver_Amps/P45_IN-: U205.6 (-), U205.7; also elsewhere on the board
/RX_Driver_Amps/P90_IN+: U202.1, U202.2 (-); also elsewhere on the board
/RX_Driver_Amps/P90_IN-: U202.6 (-), U202.7; also elsewhere on the board
/RX_Driver_Amps/P135_IN+: U208.1, U208.2 (-); also elsewhere on the board
/RX_Driver_Amps/P135_IN-: U208.6 (-), U208.7; also elsewhere on the board
/Rx_mixer/Baseband_0: HC_201.1, U201.3 (+), U203.3 (1B), U203.6 (2B)
/Rx_mixer/Baseband_45: HC_203.1, U204.3 (1B), U204.6 (2B), U205.3 (+)
/Rx_mixer/Baseband_90: HC_202.1, U202.3 (+), U203.8 (3B), U203.11 (4B)
/Rx_mixer/Baseband_135: HC_204.1, U204.8 (3B), U204.11 (4B), U208.3 (+)
/Rx_mixer/Baseband_180: HC_205.1, U201.5 (+), U206.3 (1B), U206.6 (2B)
/Rx_mixer/Baseband_225: HC_206.1, U205.5 (+), U206.8 (3B), U206.11 (4B)
/Rx_mixer/Baseband_270: HC_207.1, U202.5 (+), U207.3 (1B), U207.6 (2B)
/Rx_mixer/Baseband_315: HC_208.1, U207.8 (3B), U207.11 (4B), U208.5 (+)
/Rx_mixer/RF+: U203.2 (1A), U203.9 (3A), U204.2 (1A), U204.9 (3A), U206.2 (1A), U206.9 (3A), U207.2 (1A), U207.9 (3A); also elsewhere on the board
/Rx_mixer/RF-: U203.5 (2A), U203.12 (4A), U204.5 (2A), U204.12 (4A), U206.5 (2A), U206.12 (4A), U207.5 (2A), U207.12 (4A); also elsewhere on the board

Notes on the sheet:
Rx Math (1:1 Impedance Ratio): Rsource​=50Ω Rswitch​= close to zero Rtotal​=50Ω N=1 Effective R for bandwidth: N x R = 50 ohm BW = 1 / (2* pi * N * Reff * C) For 96 kHz BW: C= 1 / (2 * pi * 4 * 85 * 96000)​ = 33nF
